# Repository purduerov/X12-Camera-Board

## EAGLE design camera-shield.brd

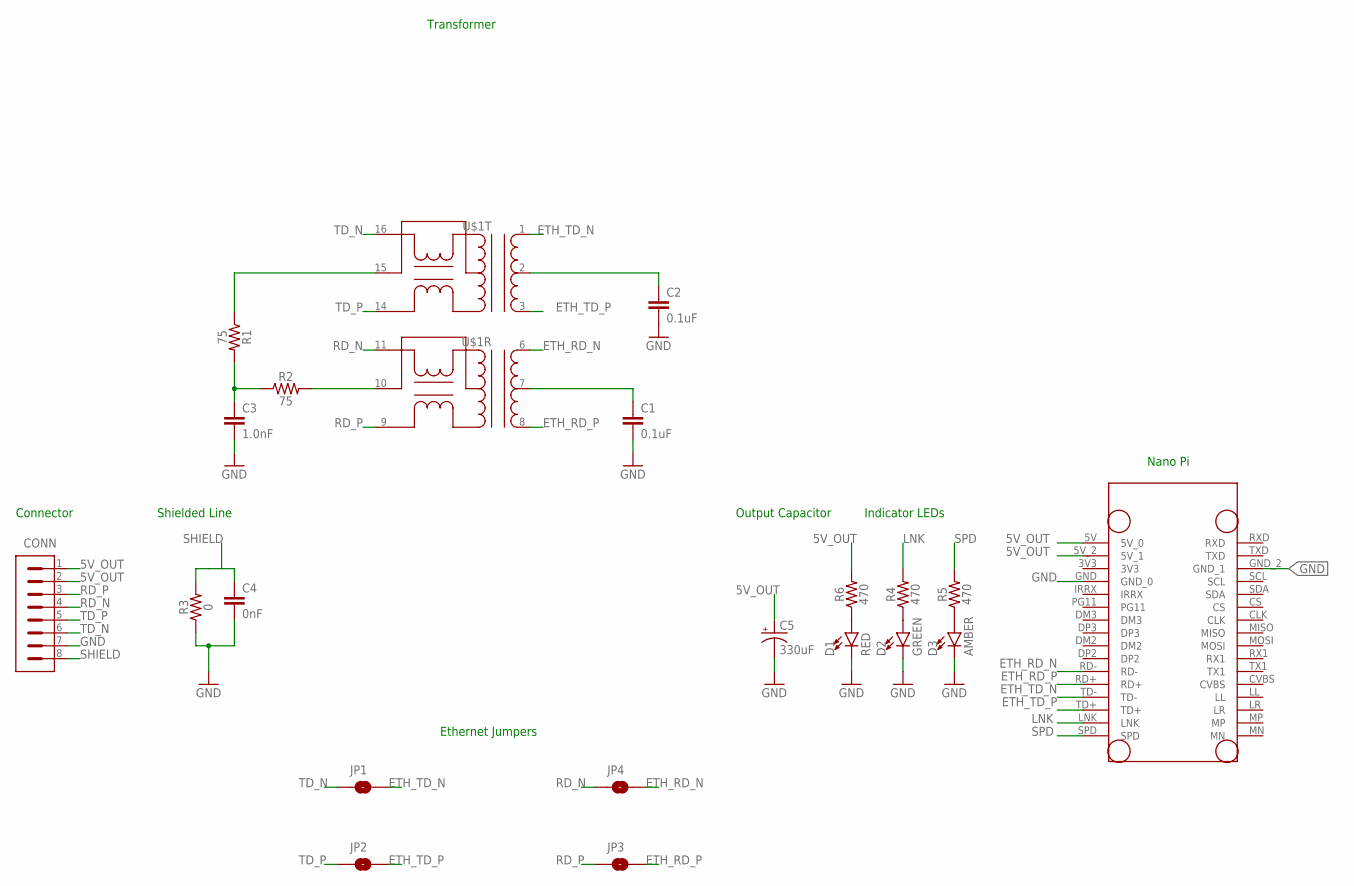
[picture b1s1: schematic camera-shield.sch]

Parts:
C1, C2: 0.1uF; 0603
C3: 1.0nF; 1206
C4: 0nF; 0603
C5: 337AXZ025M
CONN: PXC-8-RA-1778683
D1: RED; FKIT-LED-1206
D2: GREEN; FKIT-LED-1206
D3: AMBER; FKIT-LED-1206
JP1, JP2, JP3, JP4: JUMPER-SMT_2_NO_NO-SILK; SMT-JUMPER_2_NO_NO-SILK
R1, R2: 75; 0603
R3: 0; 0603
R4, R5, R6: 470; 0603
U$1: ETH-TRANS; SOIC-16-WIDE
U$2: NANO_PI_CLEAN

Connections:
5V_OUT: C5.PLUS (+), CONN.1, CONN.2, R6.2, U$2.5V (5V_0), U$2.5V_2 (5V_1)
ETH_RD_N: JP4.2, U$1.6 (D+), U$2.RD-
ETH_RD_P: JP3.2, U$1.8 (D-), U$2.RD+
ETH_TD0_GND: C1.1, U$1.7 (CT)
ETH_TD1_GND: C2.1, U$1.2 (CT)
ETH_TD_N: JP1.2, U$1.1 (D+), U$2.TD-
ETH_TD_P: JP2.2, U$1.3 (D-), U$2.TD+
GND: C1.2, C2.2, C3.2, C4.2, C5.MINUS (-), CONN.7, D1.C, D2.C, D3.C, R3.1, U$2.GND (GND_0), U$2.GND_2 (GND_1)
LNK: R4.2, U$2.LNK
unnamed: D2.A, R4.1
unnamed: D3.A, R5.1
unnamed: R2.2, U$1.10 (XCT)
unnamed: C3.1, R1.2, R2.1
unnamed: D1.A, R6.1
unnamed: R1.1, U$1.15 (XCT)
RD_N: CONN.4, JP4.1, U$1.11 (X+)
RD_P: CONN.3, JP3.1, U$1.9 (X-)
SHIELD: C4.1, CONN.8, R3.2
SPD: R5.2, U$2.SPD
TD_N: CONN.6, JP1.1, U$1.16 (X+)
TD_P: CONN.5, JP2.1, U$1.14 (X-)

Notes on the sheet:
Connector
Shielded Line
Transformer
Output Capacitor
Indicator LEDs
Nano Pi
Ethernet Jumpers

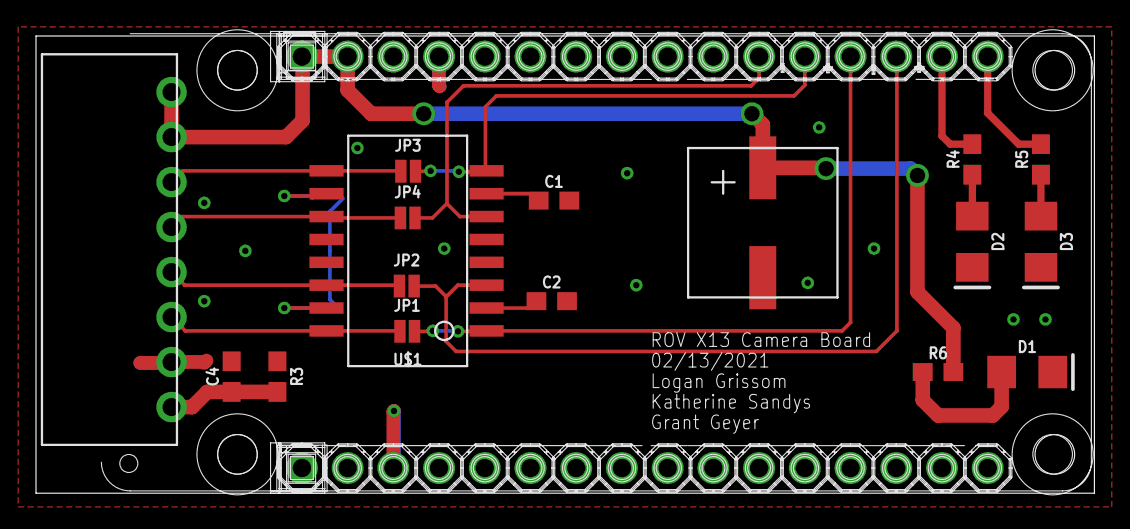
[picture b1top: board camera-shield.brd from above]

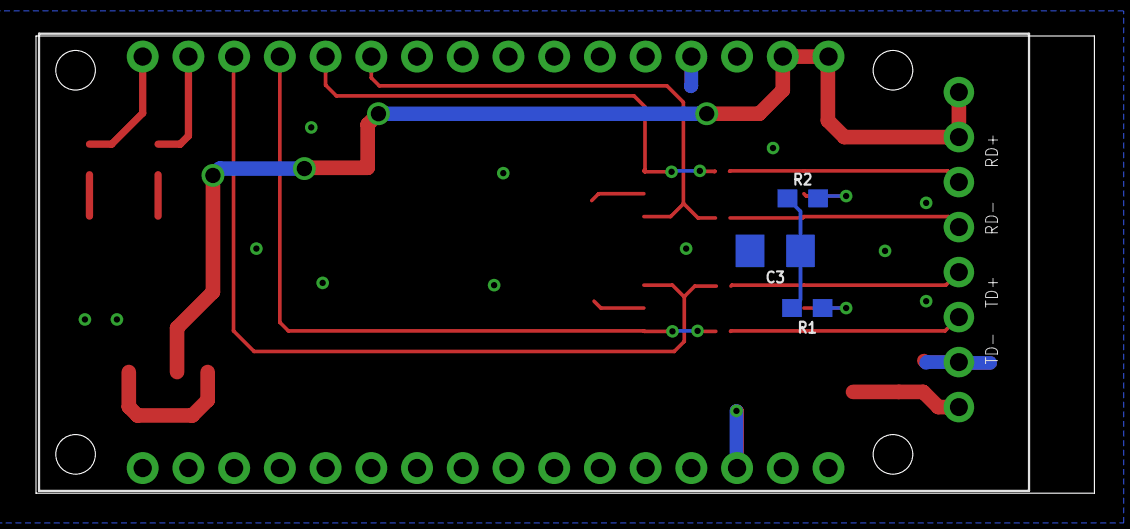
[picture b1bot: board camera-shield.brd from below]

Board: 2 copper layers, 58.8 x 25.4 mm, 21 parts (4 on the bottom side), 21 nets.

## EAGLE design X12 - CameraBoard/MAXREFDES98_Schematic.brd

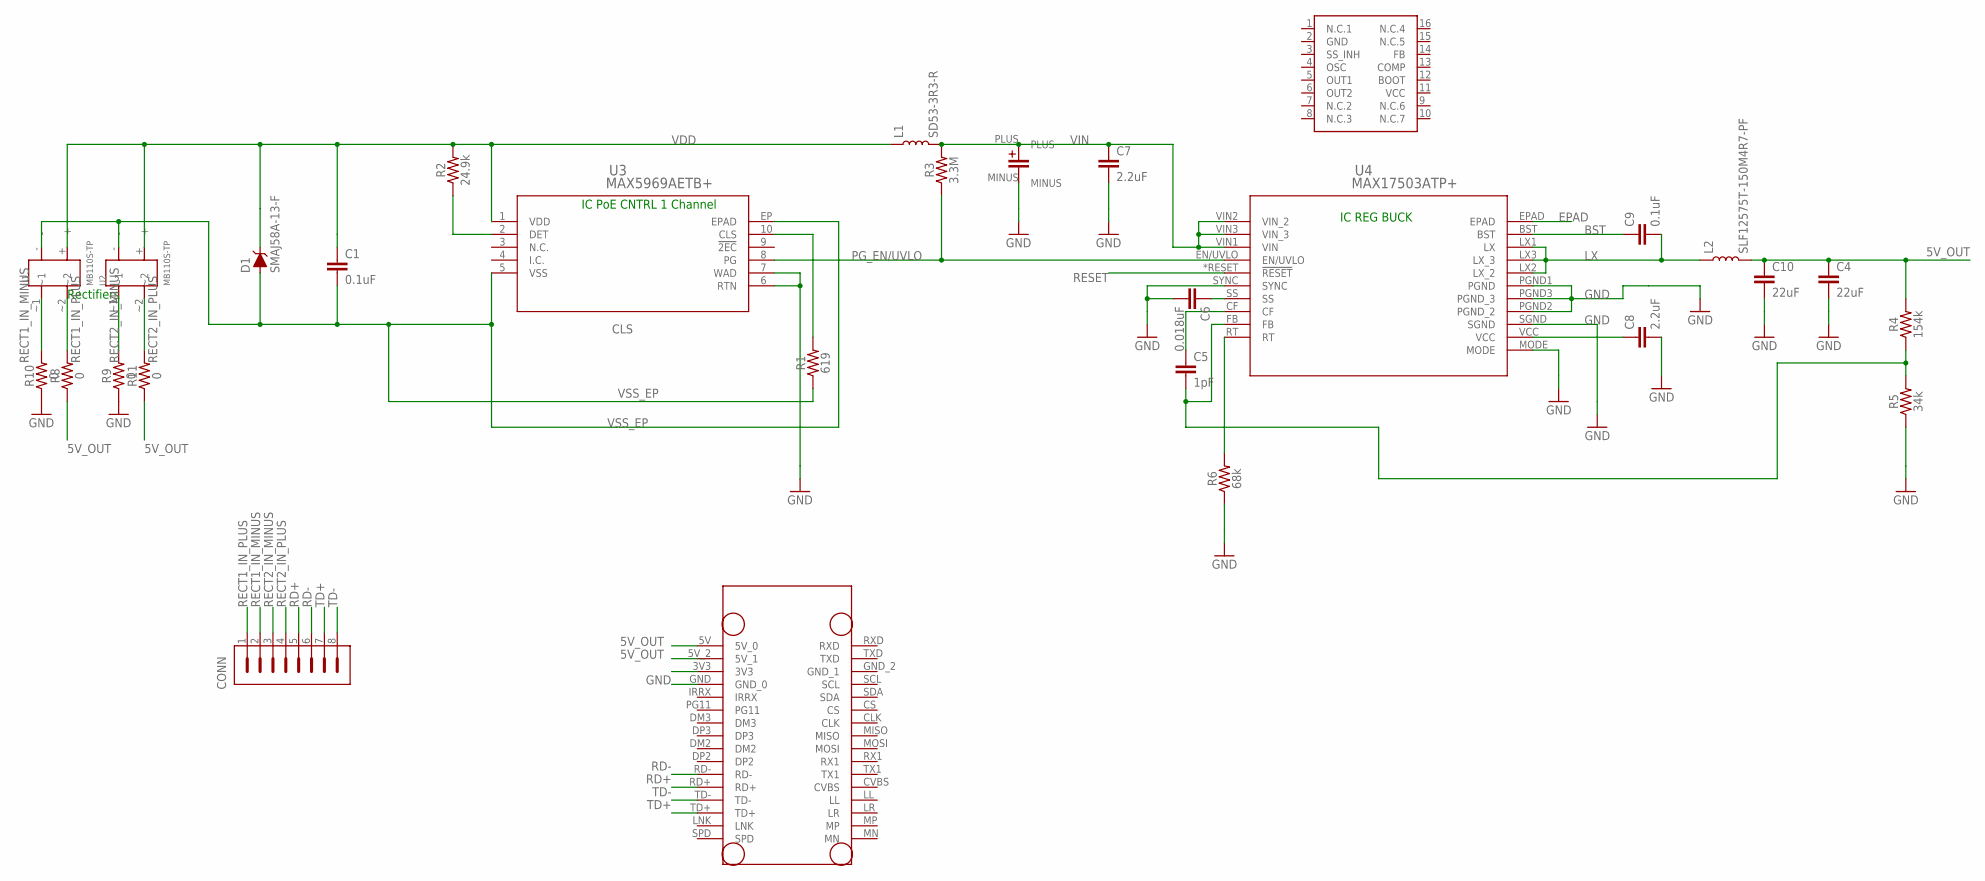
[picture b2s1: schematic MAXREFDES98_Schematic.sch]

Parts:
C1: 0.1uF; 0805
C2: EEE-1JA220UP
C4, C10: 22uF; 1210
C5: 1pF; 0603
C6: 0.018uF; 0603
C7: 2.2uF; 1210
C8: 2.2uF; 0603
C9: 0.1uF; 0603
CONN: TERM_BLOCK_PLUG_8POS_STR_2.5MM
D1: SMAJ58A-13-F
L1: SD53-3R3-R
L2: SLF12575T-150M4R7-PF
R1: 619; 0603
R2: 24.9k; 0603
R3: 3.3M; 0603
R4: 154k; 0603
R5: 34k; 0603
R6: 68k; 0603
R8, R9, R10, R11: 0; 0603
U1, U2: MB110S-TP
U3: MAX5969AETB+
U4: MAX17503ATP+
U$1: L4978D013TR
U$2: NANO_PI

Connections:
5V_OUT: C4.1, C10.1, L2.P$2 (2), R4.2, R8.1, R11.1, U$2.5V (5V_0), U$2.5V_2 (5V_1)
BST: C9.1, U4.BST
CF: C5.1, U4.CF
CLS: R1.2, U3.10 (CLS)
DET: R2.1, U3.2 (DET)
EPAD: U4.EPAD
FB: C5.2, R4.1, R5.2, U4.FB
GND: C2.MINUS, C4.2, C6.2, C7.2, C8.2, C10.2, R5.1, R6.1, R9.1, R10.1, U3.6 (RTN), U3.7 (WAD), U4.MODE, U4.PGND1 (PGND), U4.PGND2 (PGND_2), U4.PGND3 (PGND_3), U4.SGND, U4.SYNC, U$2.GND (GND_0)
LX: C9.2, L2.P$1 (1), U4.LX1 (LX), U4.LX2 (LX_2), U4.LX3 (LX_3)
PG_EN/UVLO: R3.1, U3.8 (PG), U4.EN/UVLO
RD+: CONN.5, U$2.RD+
RD-: CONN.6, U$2.RD-
RECT1_IN_MINUS: CONN.2, R10.2, U1.~1
RECT1_IN_PLUS: CONN.1, R8.2, U1.~2
RECT2_IN_MINUS: CONN.3, R9.2, U2.~1
RECT2_IN_PLUS: CONN.4, R11.2, U2.~2
RESET: U4.*RESET (!RESET)
RT: R6.2, U4.RT
SS: C6.1, U4.SS
TD+: CONN.7, U$2.TD+
TD-: CONN.8, U$2.TD-
VCC: C8.1, U4.VCC
VDD: C1.1, D1.P$1 (1), L1.P$1 (1), R2.2, U1.+, U2.+, U3.1 (VDD)
VIN: C2.PLUS, C7.1, L1.P$2 (2), R3.2, U4.VIN1 (VIN), U4.VIN2 (VIN_2), U4.VIN3 (VIN_3)
VSS_EP: C1.2, D1.P$2 (2), R1.1, U1.-, U2.-, U3.5 (VSS), U3.EP (EPAD)

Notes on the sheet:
IC PoE CNTRL 1 Channel
IC REG BUCK
Rectifiers

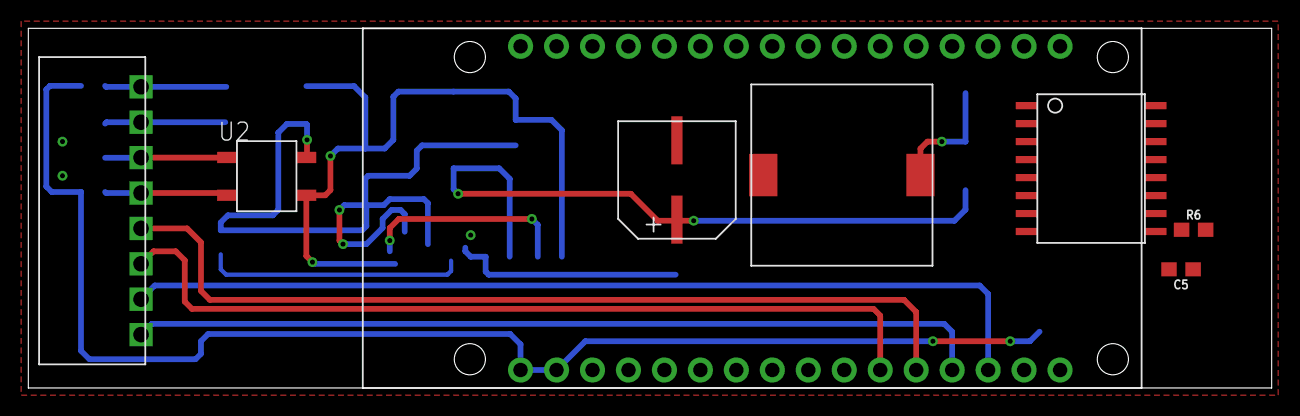
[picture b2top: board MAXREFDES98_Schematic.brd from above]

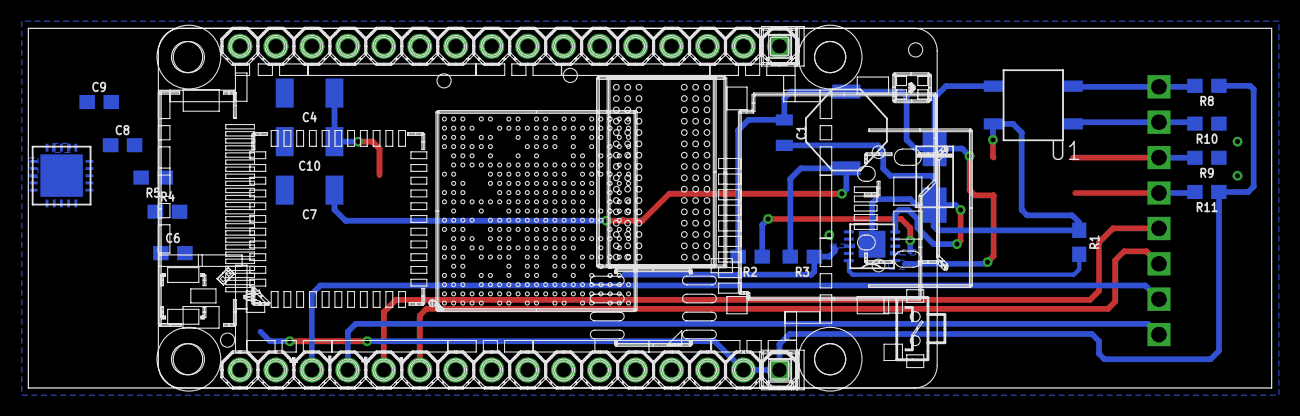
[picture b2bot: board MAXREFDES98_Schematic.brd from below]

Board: 2 copper layers, 87.8 x 25.4 mm, 29 parts (21 on the bottom side), 23 nets.

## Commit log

2019-11-09 Files
    Added Files
2019-12-31 Board Down-Scaling
    Scaled board down to 500 mil in width and moved all large components to one side of the board.
2020-01-18 Update MAXREFDES98_Schematic.brd
    Fixed Airwires and other misc. DRC errors.
2020-04-03 fixed those darn backups
2020-04-03 added git ignore
2020-09-12 Added Net Labels & Mounting Holes
2020-09-13 added gitignore to master
2020-09-19 rewiring
2020-09-19 Update MAXREFDES98_Schematic.brd
    Changed mounting holes to be right size and place on board, according to NanoPi board.
2020-09-24 Update MAXREFDES98_Schematic.brd
    Added IC chip descriptions
2020-09-25 Reconfigured Board Layout
    Reconfigured Board Layout
2020-09-26 Update MAXREFDES98_Schematic.brd
    rerouting
2020-09-26 Update MAXREFDES98_Schematic.sch
    Added frame and better labels
2020-09-26 Update MAXREFDES98_Schematic.brd
    routing
2020-09-26 Update MAXREFDES98_Schematic.brd
    I know there are spacing issues with some traces, but I have not figured out how wide they need to be; so, I have made them larger than I think they need to be, for now.
2020-09-26 Update MAXREFDES98_Schematic.brd
    fixed wire stub issues
2020-10-03 Create Camera_Board_Parts_09_30_2020.lbr
    Added Nano Pi Duo 2 and Phoenix Connector parts
2020-10-09 Added New Connector and PI
2020-10-09 Update Camera_Board_Parts_09_30_2020.lbr
    Updated parts
2020-10-10 Added 0 Ohm Resistor amd 1-pin connector directly to 5V line
2020-10-10 Rerouting
    Almost done, just need some clarification on the signals connected to the 8-pin connector before I try routing those. If the signals are as I assumed, the 8-pin connector might need to move to the ot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
2020-10-16 Rerouting
2020-10-22 Fixing 0-Ohm Resistor stuff
2020-10-23 Added New Buck Regultor (needs to be connected with new supporting circuitry)
2020-10-24 Routing
    Definetely need to change buck regulator because of spacing and soldering issues. Will do that soonish.
2020-10-25 Move everything from folder. Add 3D model for connector
2020-10-30 Added new buck converter, plus supporting circuitry
2020-10-31 Conneted PG_EN line to SS_INH and added limiting resistors for LEDs
    Need to determine if SPD/LNK lines are active high or active low.
2020-10-31 Consolidated Camera Board Library
2020-11-06 Worked on schematic/checking component values
2020-11-07 Schematic fixes, parts update, replace parts on board
2020-11-13 Added clean version of Nano Pi footprint
2020-11-20 New Caps
2020-11-21 Added new caps and leds
2020-12-06 Placement
2021-01-04 Board all wired up
    Board is all wried up, DRC is passed
    Board is also smaller now as well
2021-01-05 minor changes
2021-01-05 5V_out line changed
    also flipped soething to the back along with wire thickness changed
2021-01-09 re-route ethernet. clean up a few things
2021-01-21 Added GND to Buck and changed some wire widths.
2021-01-29 Deleted PoE and added Transformer
2021-02-06 Updated board with transformer circuit and new connector signals
2021-02-13 Added schematic labels, 1206 cap, fixed ethernet line width
2021-02-13 Added Power Indicator LED, shortened board
2021-02-13 Added text
2021-02-13 Changed text layer
2021-02-14 Added ethernet jumpers
2021-02-16 Increased 5V via size, updated text
2021-02-17 Flip ethernet termination, use transformer symbol, clean up repo a little

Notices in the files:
parts and their libraries:
SparkFun-Capacitors: Licensing: Creative Commons ShareAlike 4.0 International - https://creativecommons.org/licenses/by-sa/4.0
